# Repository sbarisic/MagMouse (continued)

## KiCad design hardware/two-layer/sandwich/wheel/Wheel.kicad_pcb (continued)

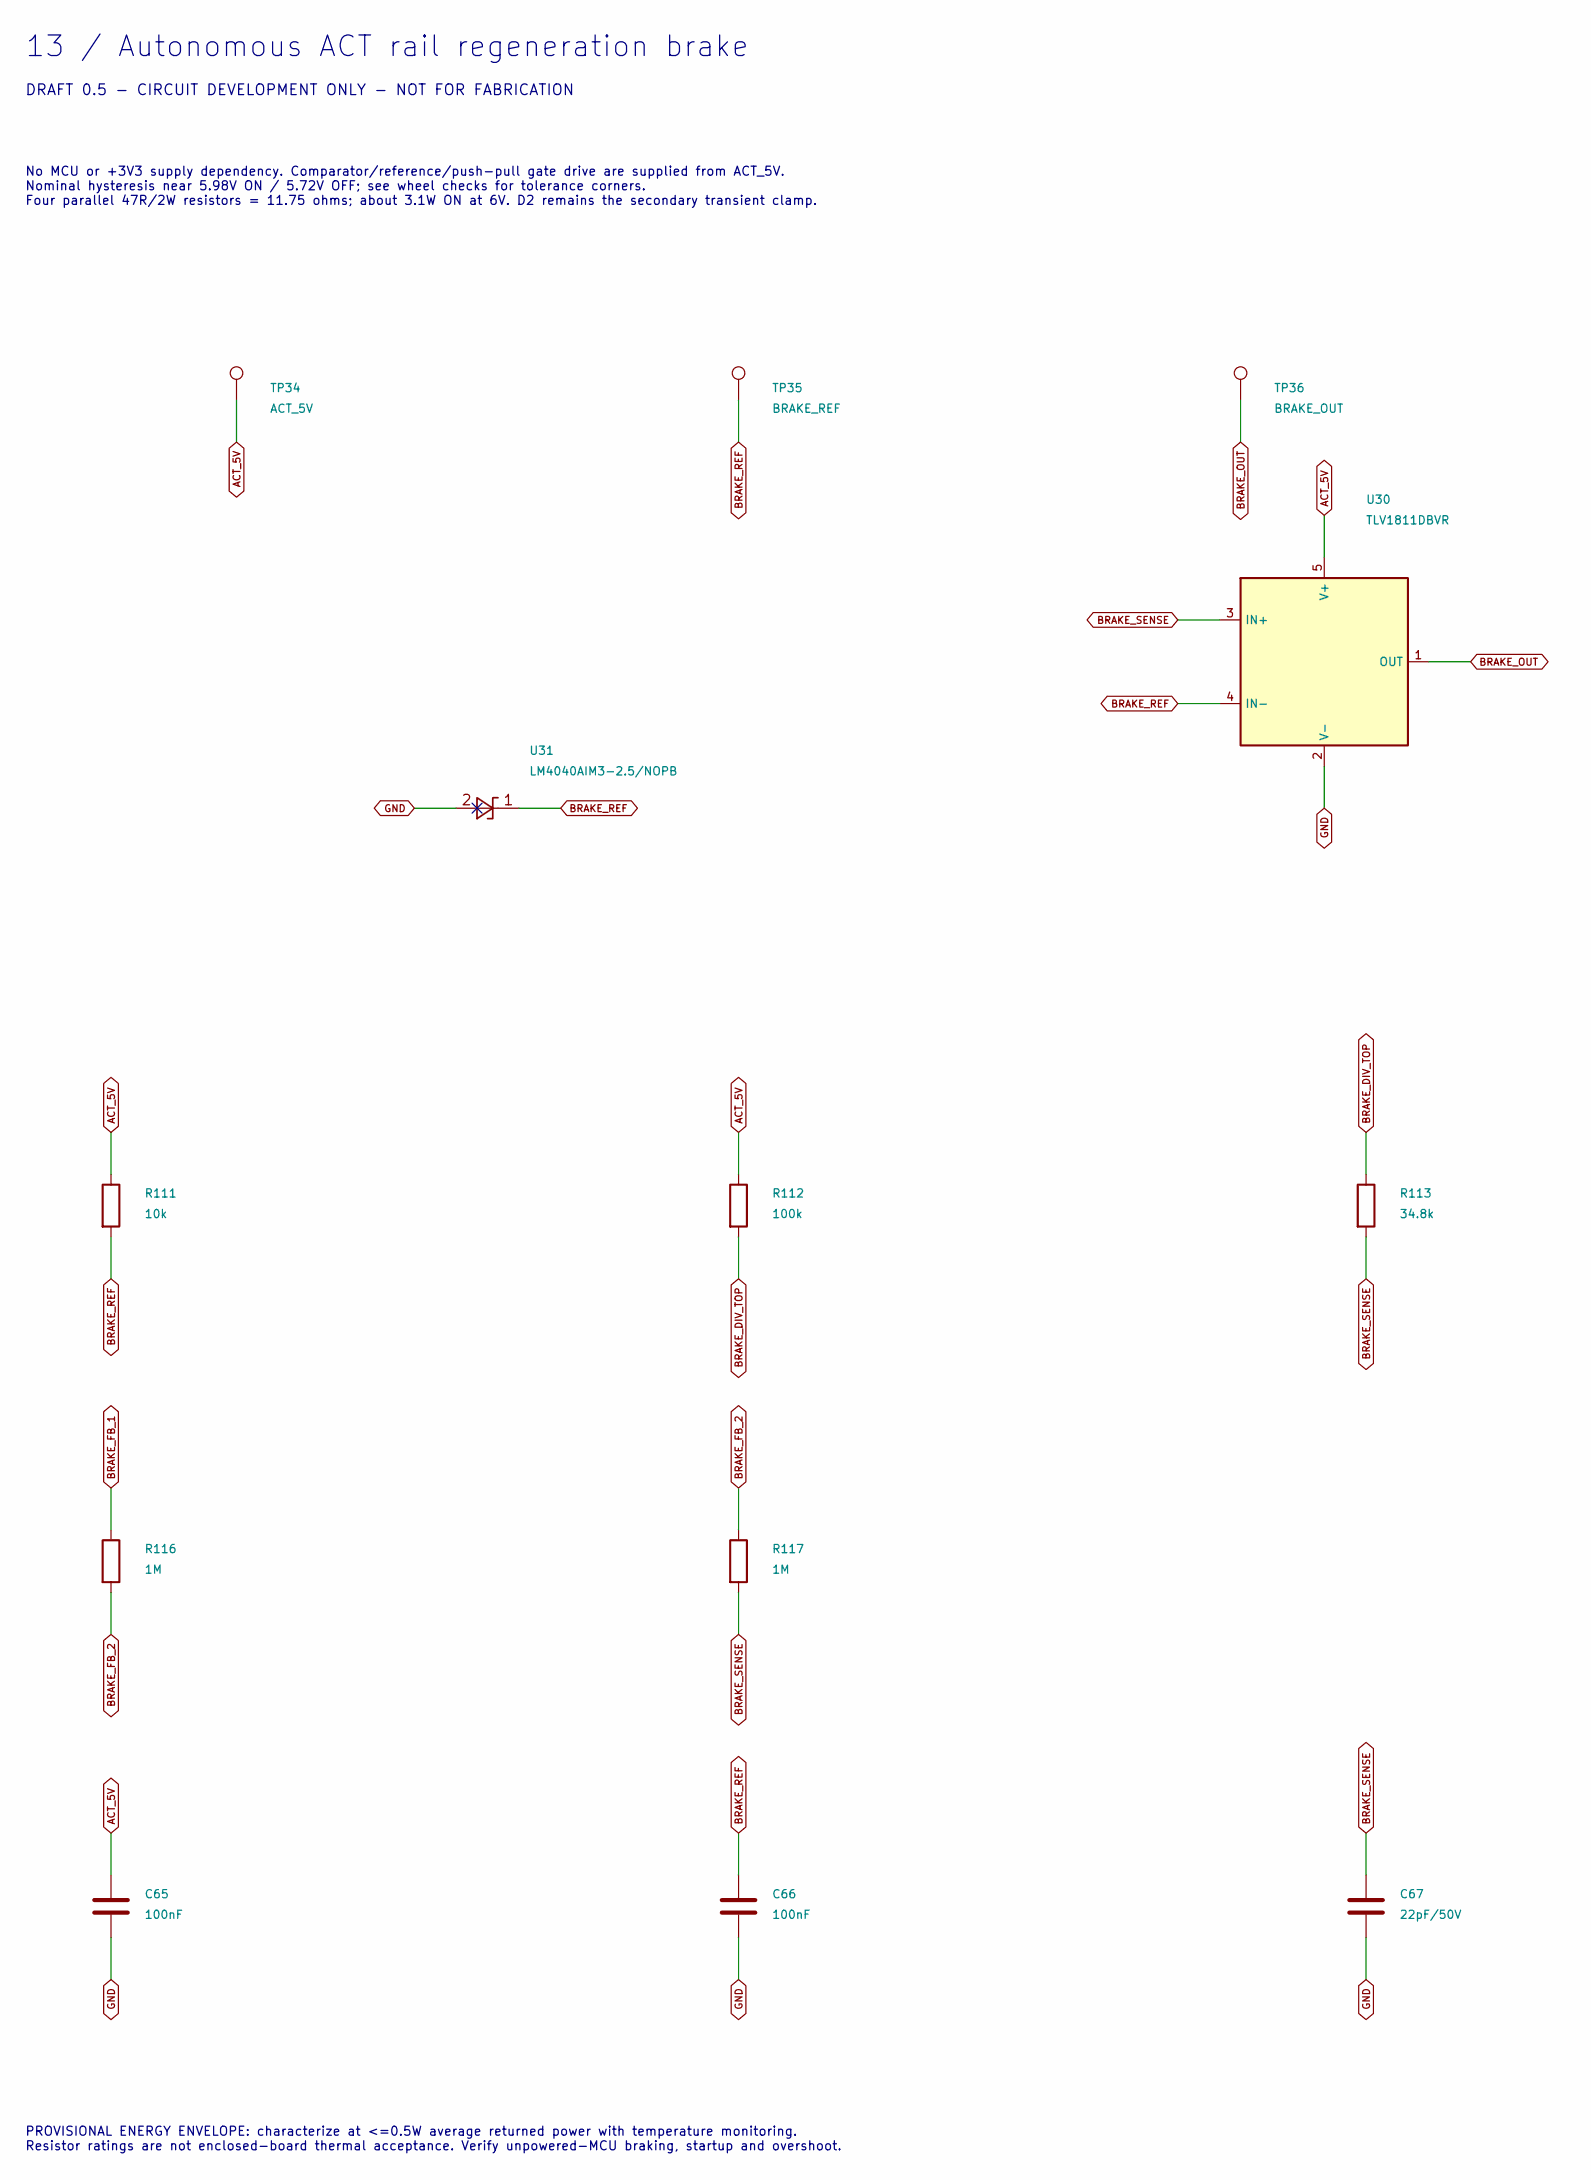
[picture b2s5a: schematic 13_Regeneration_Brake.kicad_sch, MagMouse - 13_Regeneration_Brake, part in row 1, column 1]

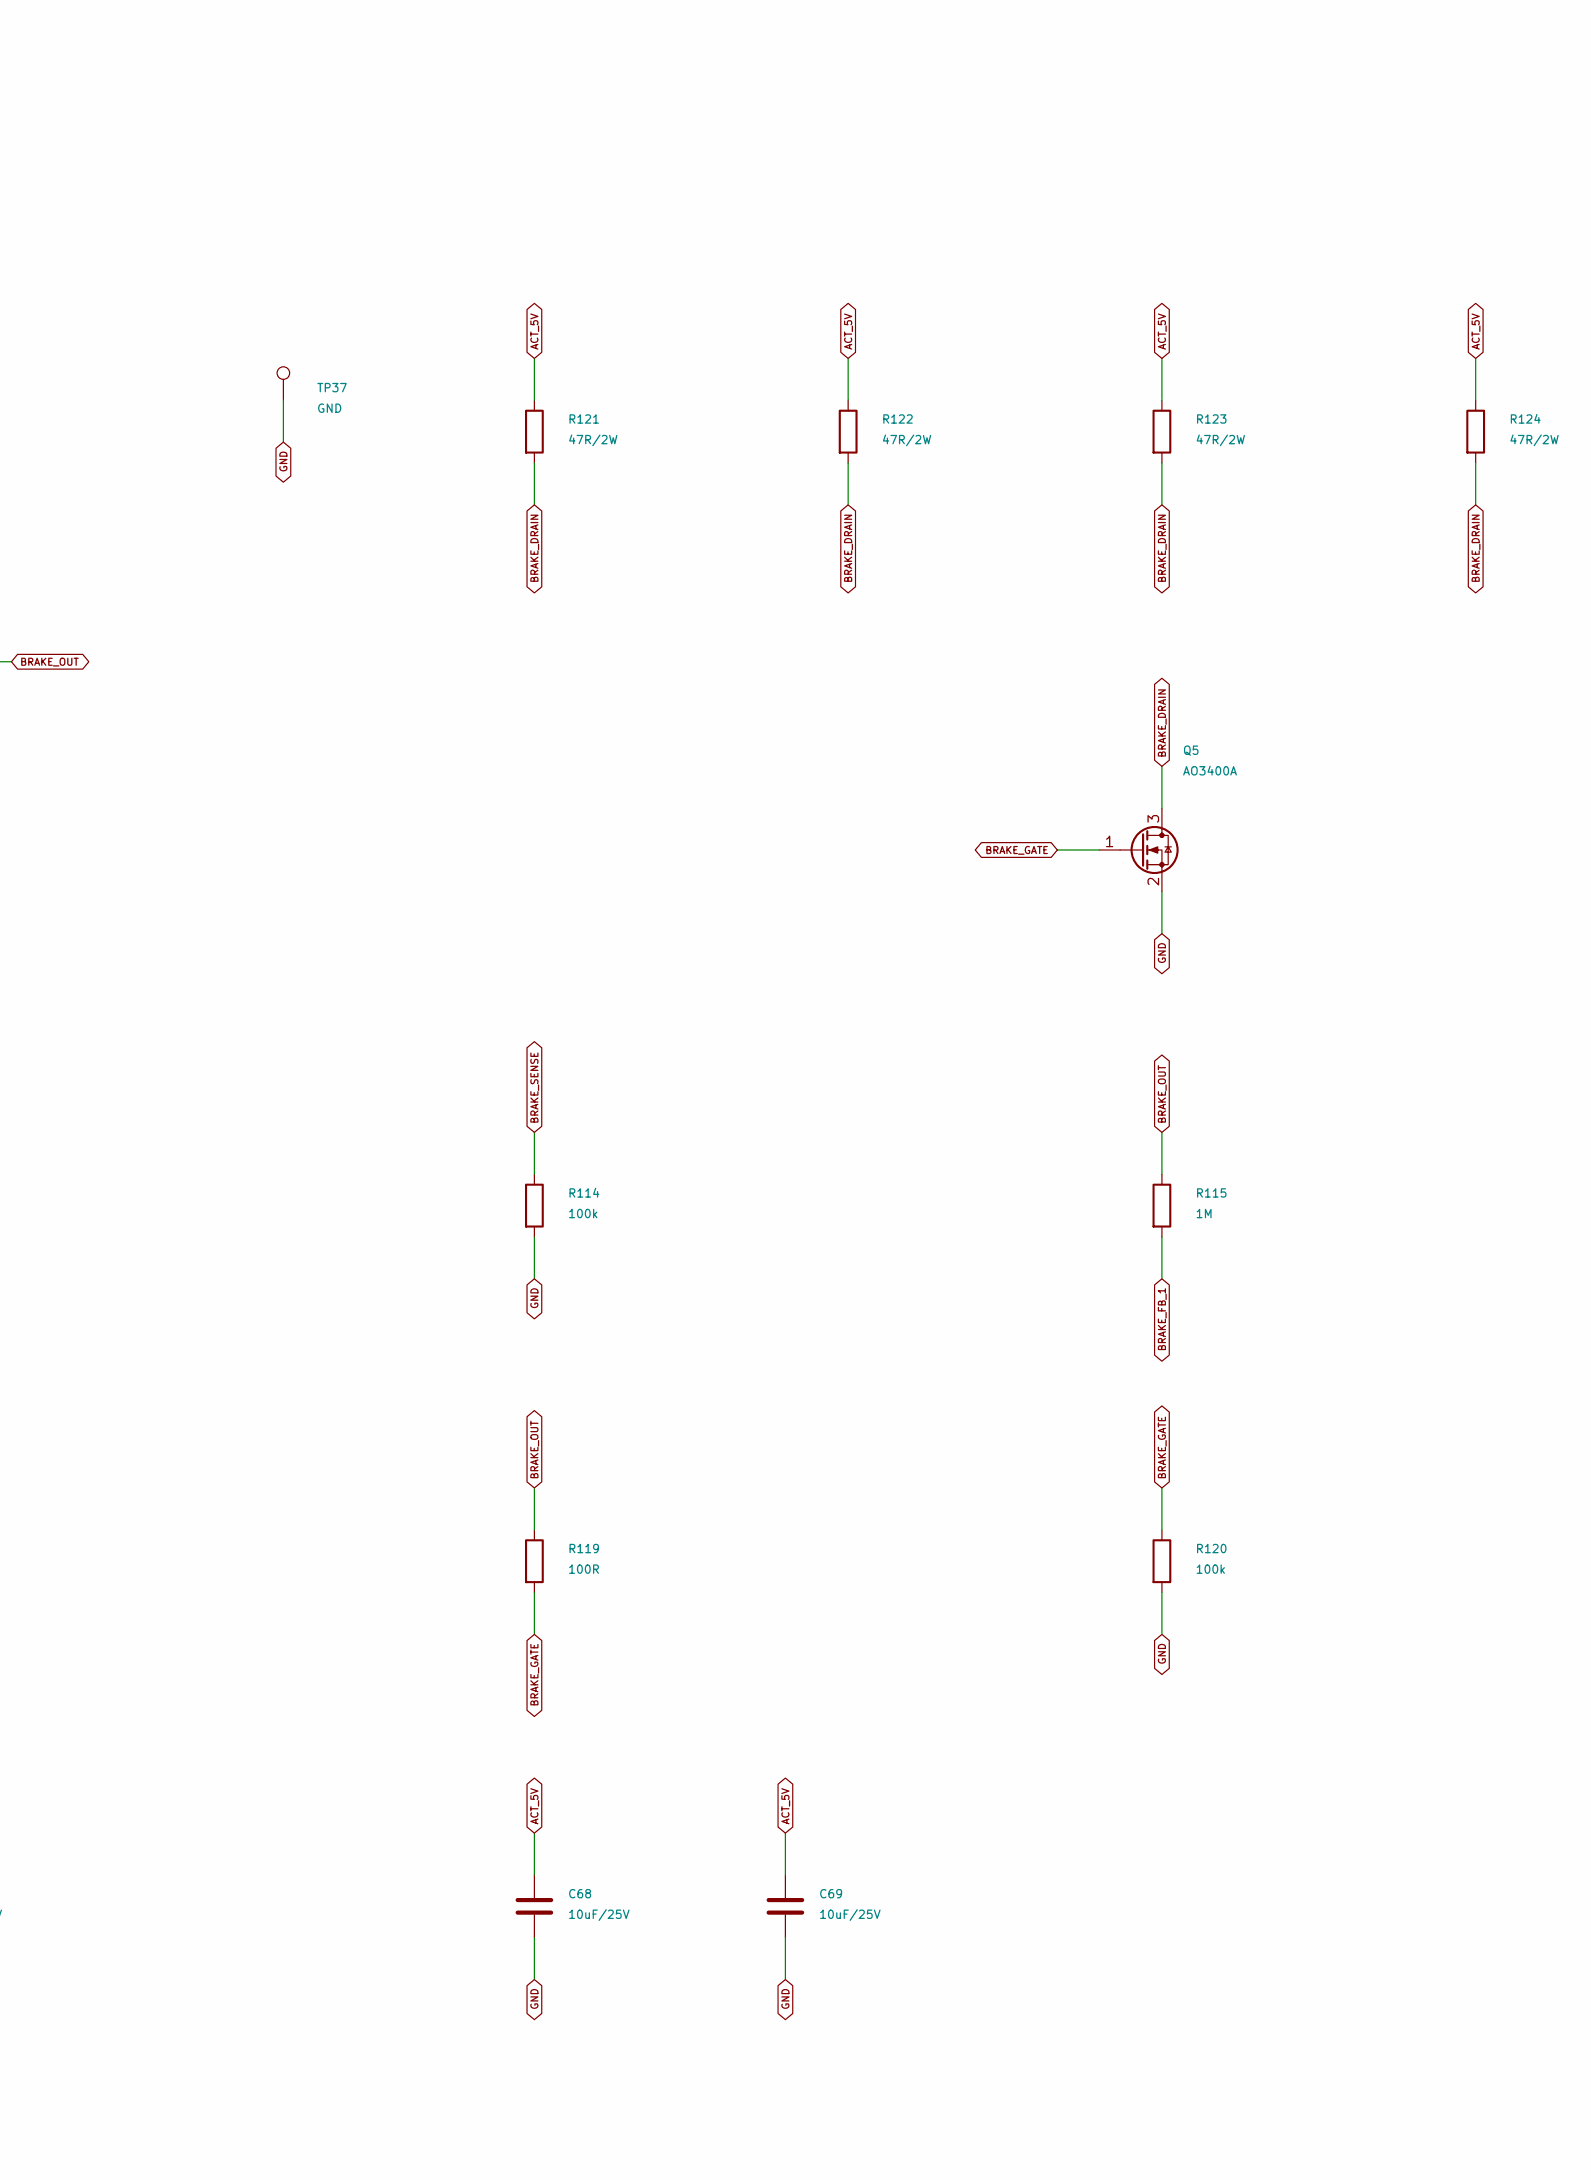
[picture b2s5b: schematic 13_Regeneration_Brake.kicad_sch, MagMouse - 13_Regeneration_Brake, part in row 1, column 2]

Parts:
C65, C66: 100nF; C_1206_3216Metric; Rating 50 V, X7R, 10%; MPN CC1206KRX7R9BB104
C67: 22pF/50V; C_1206_3216Metric; Rating 50 V, C0G/NP0, 5%; MPN CC1206JRNPO9BN220
C68, C69: 10uF/25V; C_1206_3216Metric; Rating 25 V, X5R, 10%; MPN CL31A106KAHNNNE
Q5: AO3400A; SOT-23; MPN AO3400A; LCSC C20917
R111: 10k; R_1206_3216Metric; Rating 0.25 W, 1%; MPN RC1206FR-0710KL
R112, R114, R120: 100k; R_1206_3216Metric; Rating 0.25 W, 1%; MPN RC1206FR-07100KL
R113: 34.8k; R_1206_3216Metric; Rating 0.25 W, 1%; MPN RC1206FR-0734K8L
R115, R116, R117: 1M; R_1206_3216Metric; Rating 0.25 W, 1%; MPN RC1206FR-071ML
R119: 100R; R_1206_3216Metric; Rating 0.25 W, 1%; MPN RC1206FR-07100RL
R121, R122, R123, R124: 47R/2W; R_2512_6332Metric; MPN RC2512JK-7W47RL; LCSC C136992
TP34: ACT_5V; TestPoint_Pad_D1.0mm
TP35: BRAKE_REF; TestPoint_Pad_D1.0mm
TP36: BRAKE_OUT; TestPoint_Pad_D1.0mm
TP37: GND; TestPoint_Pad_D1.0mm
U30: TLV1811DBVR; SOT-23-5; MPN TLV1811DBVR; LCSC C5373003
U31: LM4040AIM3-2.5/NOPB; SOT-23; MPN LM4040AIM3-2.5/NOPB; LCSC C139302

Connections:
ACT_5V: C65.1, C68.1, C69.1, R111.1, R112.1, R121.1, R122.1, R123.1, R124.1, TP34.1, U30.5 (V+); also elsewhere on the board
BRAKE_DIV_TOP: R112.2, R113.1
BRAKE_DRAIN: Q5.3 (D), R121.2, R122.2, R123.2, R124.2
BRAKE_FB_1: R115.2, R116.1
BRAKE_FB_2: R116.2, R117.1
BRAKE_GATE: Q5.1 (G), R119.2, R120.1
BRAKE_OUT: R115.1, R119.1, TP36.1, U30.1 (OUT)
BRAKE_REF: C66.1, R111.2, TP35.1, U30.4 (IN-), U31.1 (K)
BRAKE_SENSE: C67.1, R113.2, R114.1, R117.2, U30.3 (IN+)
GND: C65.2, C66.2, C67.2, C68.2, C69.2, Q5.2 (S), R114.2, R120.2, TP37.1, U30.2 (V-), U31.2 (A); also elsewhere on the board

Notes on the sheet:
13 / Autonomous ACT rail regeneration brake
DRAFT 0.5 - CIRCUIT DEVELOPMENT ONLY - NOT FOR FABRICATION
No MCU or +3V3 supply dependency. Comparator/reference/push-pull gate drive are supplied from ACT_5V. Nominal hysteresis near 5.98V ON / 5.72V OFF; see wheel checks for tolerance corners. Four parallel 47R/2W resistors = 11.75 ohms; about 3.1W ON at 6V. D2 remains the secondary transient clamp.
PROVISIONAL ENERGY ENVELOPE: characterize at <=0.5W average returned power with temperature monitoring. Resistor ratings are not enclosed-board thermal acceptance. Verify unpowered-MCU braking, startup and overshoot.

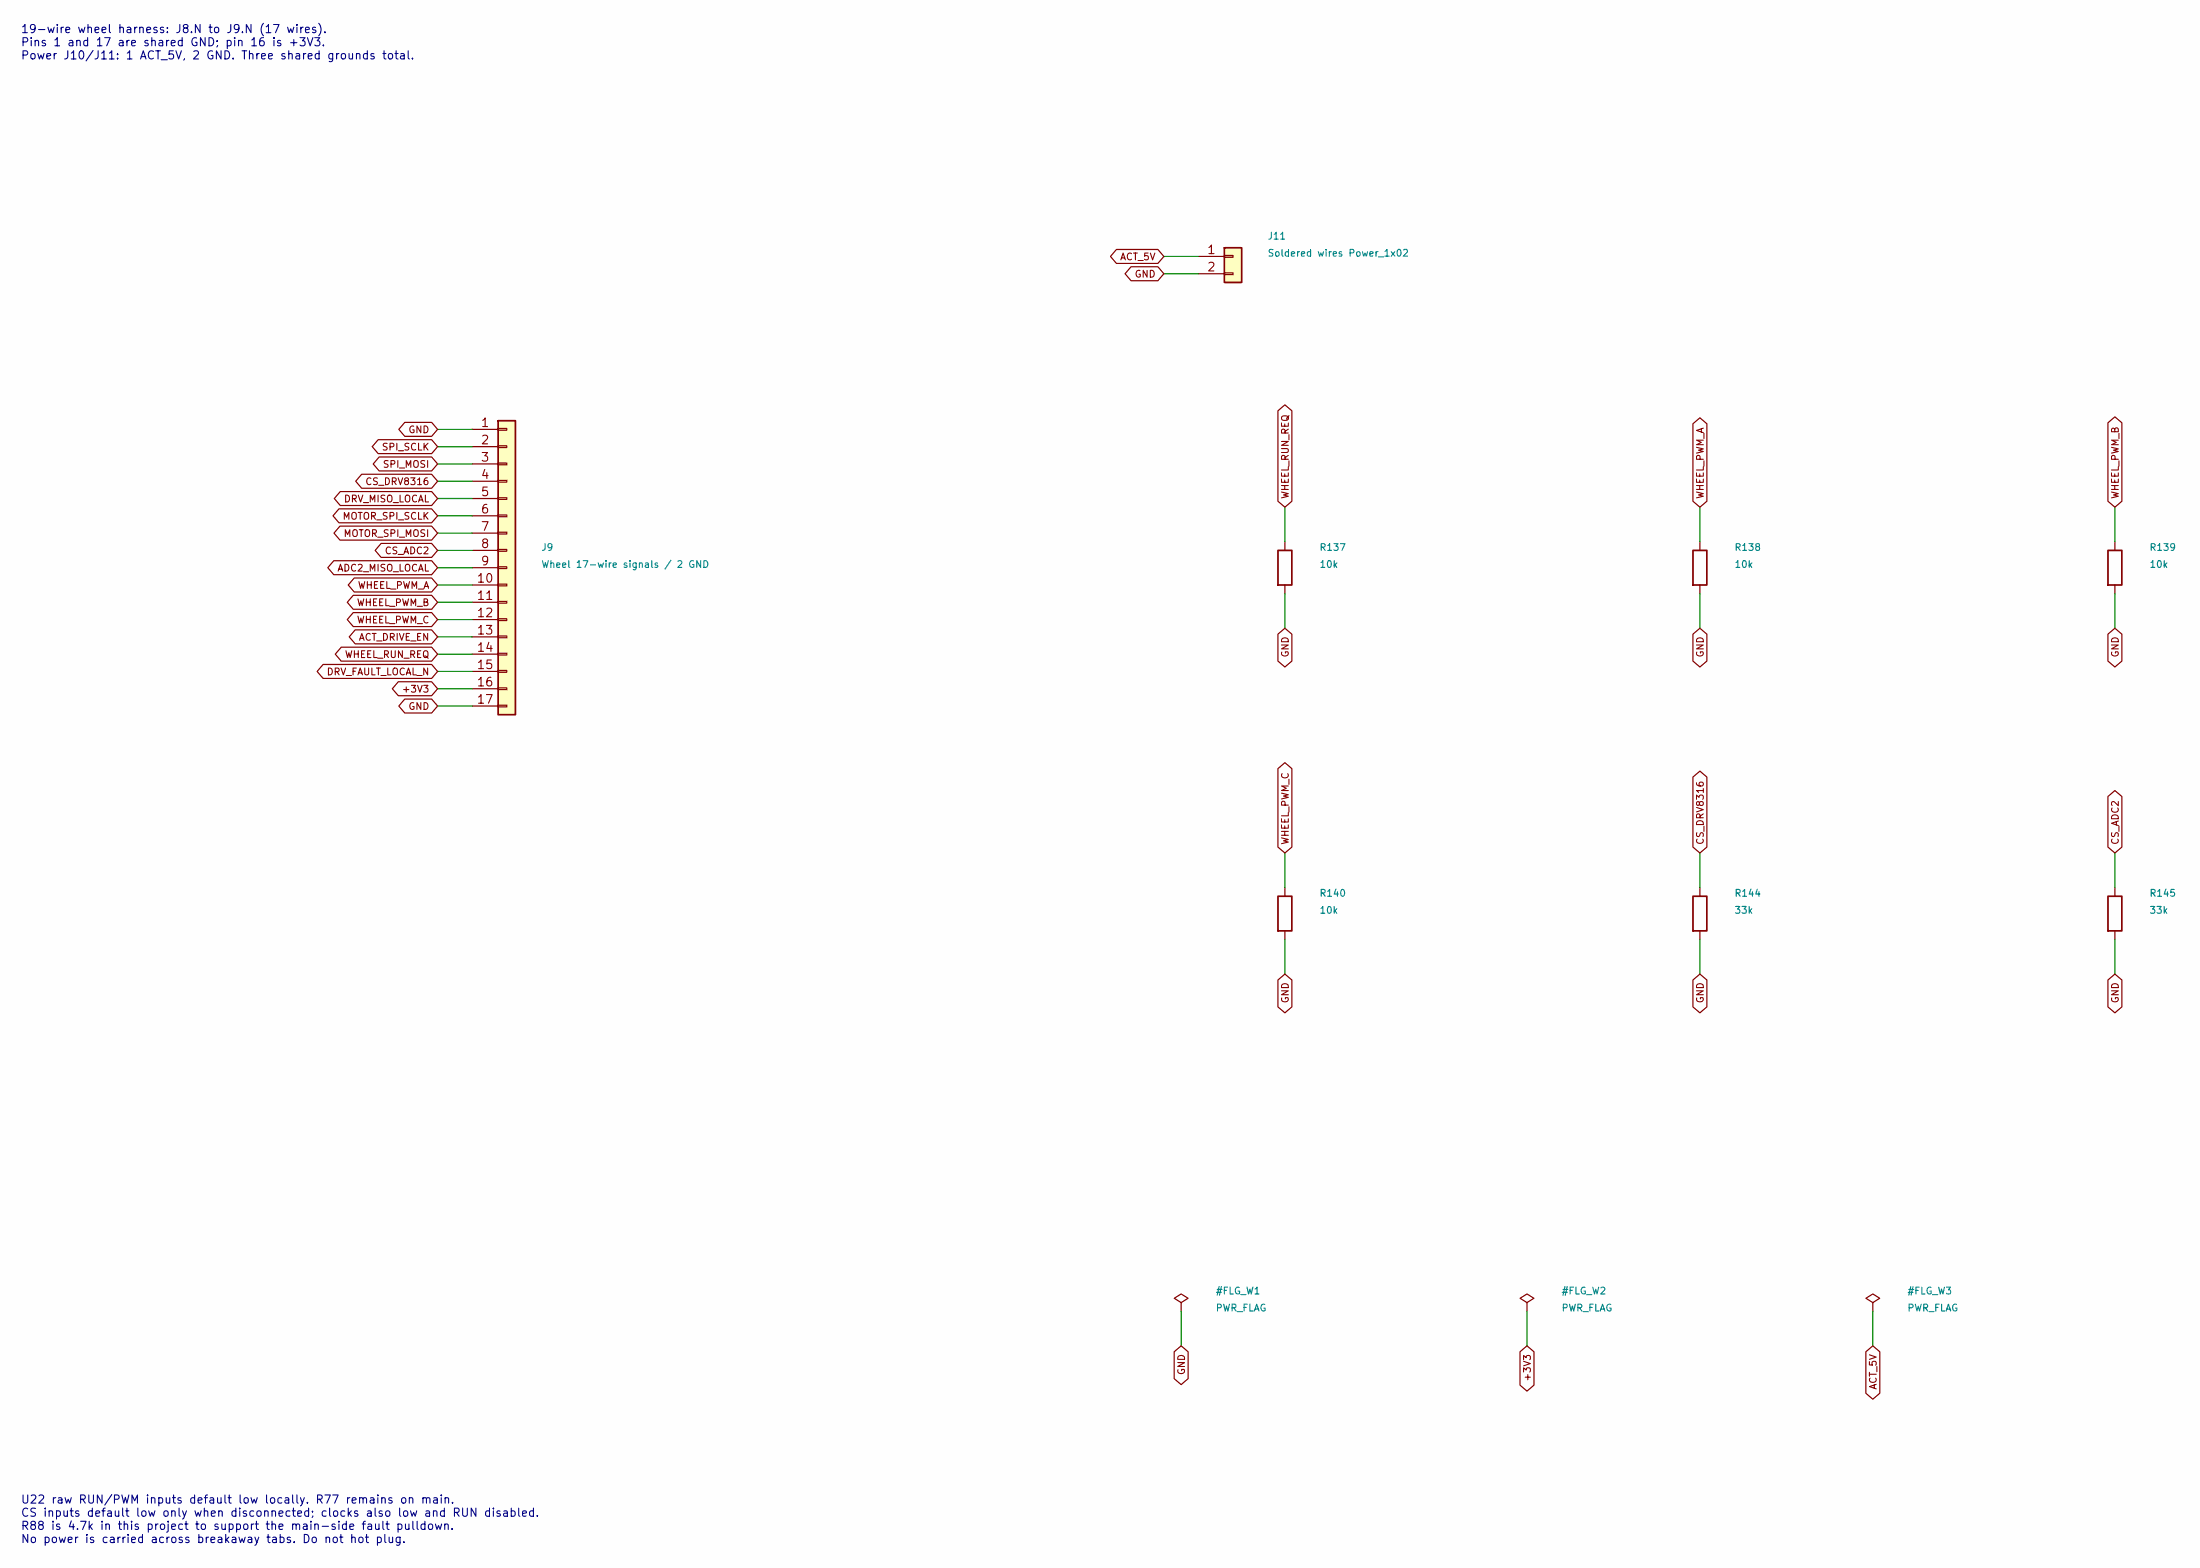
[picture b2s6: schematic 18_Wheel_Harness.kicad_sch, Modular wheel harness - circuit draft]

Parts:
J9: Wheel 17-wire signals / 2 GND; Wire_Wheel_17_P2.54mm
J11: Soldered wires Power_1x02; Wire_Power_1x02_P2.54mm
R137, R138, R139, R140: 10k; R_1206_3216Metric; Rating 0.25 W, 1%; MPN RC1206FR-0710KL
R144, R145: 33k; R_1206_3216Metric; Rating 0.25 W, 1%; MPN RC1206FR-0733KL

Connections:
+3V3: J9.16; also elsewhere on the board
ACT_5V: J11.1; also elsewhere on the board
ACT_DRIVE_EN: J9.13; also elsewhere on the board
ADC2_MISO_LOCAL: J9.9; also elsewhere on the board
CS_ADC2: J9.8, R145.1; also elsewhere on the board
CS_DRV8316: J9.4, R144.1; also elsewhere on the board
DRV_FAULT_LOCAL_N: J9.15; also elsewhere on the board
DRV_MISO_LOCAL: J9.5; also elsewhere on the board
GND: J9.1, J9.17, J11.2, R137.2, R138.2, R139.2, R140.2, R144.2, R145.2; also elsewhere on the board
MOTOR_SPI_MOSI: J9.7; also elsewhere on the board
MOTOR_SPI_SCLK: J9.6; also elsewhere on the board
SPI_MOSI: J9.3; also elsewhere on the board
SPI_SCLK: J9.2; also elsewhere on the board
WHEEL_PWM_A: J9.10, R138.1; also elsewhere on the board
WHEEL_PWM_B: J9.11, R139.1; also elsewhere on the board
WHEEL_PWM_C: J9.12, R140.1; also elsewhere on the board
WHEEL_RUN_REQ: J9.14, R137.1; also elsewhere on the board

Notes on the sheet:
19-wire wheel harness: J8.N to J9.N (17 wires). Pins 1 and 17 are shared GND; pin 16 is +3V3. Power J10/J11: 1 ACT_5V, 2 GND. Three shared grounds total.
U22 raw RUN/PWM inputs default low locally. R77 remains on main. CS inputs default low only when disconnected; clocks also low and RUN disabled. R88 is 4.7k in this project to support the main-side fault pulldown. No power is carried across breakaway tabs. Do not hot plug.

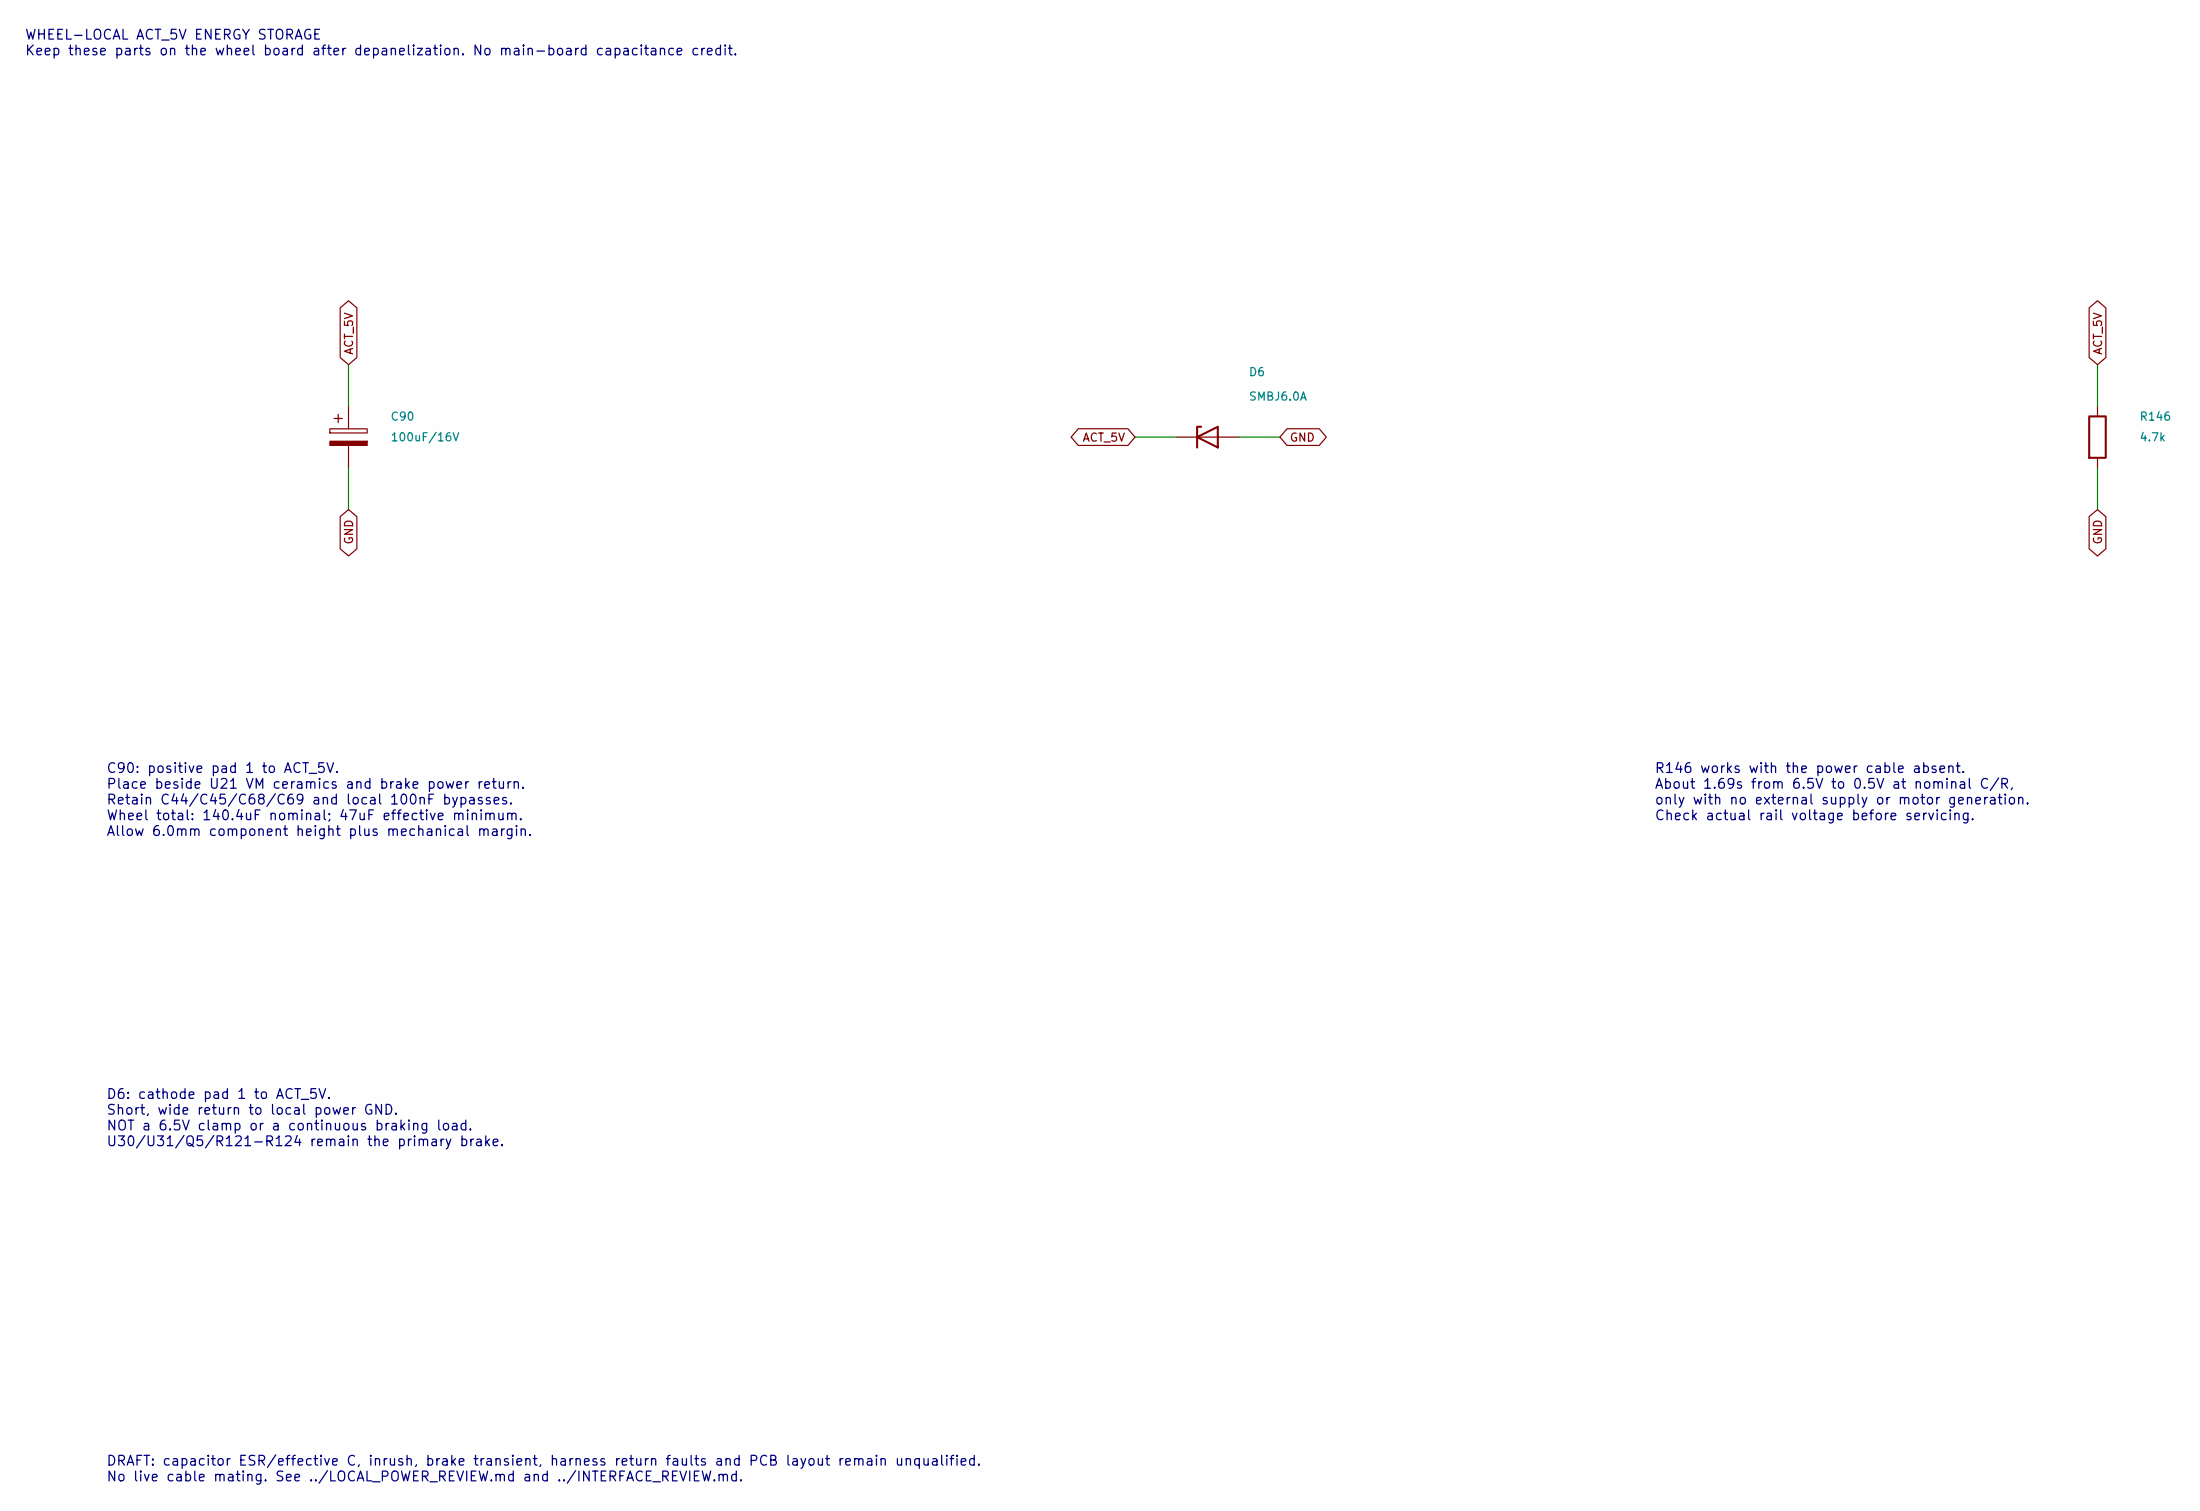
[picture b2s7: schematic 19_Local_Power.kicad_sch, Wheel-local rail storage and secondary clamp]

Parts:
C90: 100uF/16V; CP_Elec_6.3x5.9; MPN 16SVPC100M; LCSC C136275
D6: SMBJ6.0A; D_SMB; MPN SMBJ6.0A; LCSC C83270
R146: 4.7k; R_1206_3216Metric; Rating 0.25 W, 1%; MPN RC1206FR-074K7L

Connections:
ACT_5V: C90.1, D6.1 (K), R146.1; also elsewhere on the board
GND: C90.2, D6.2 (A), R146.2; also elsewhere on the board

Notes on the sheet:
WHEEL-LOCAL ACT_5V ENERGY STORAGE Keep these parts on the wheel board after depanelization. No main-board capacitance credit.
C90: positive pad 1 to ACT_5V. Place beside U21 VM ceramics and brake power return. Retain C44/C45/C68/C69 and local 100nF bypasses. Wheel total: 140.4uF nominal; 47uF effective minimum. Allow 6.0mm component height plus mechanical margin.
D6: cathode pad 1 to ACT_5V. Short, wide return to local power GND. NOT a 6.5V clamp or a continuous braking load. U30/U31/Q5/R121-R124 remain the primary brake.
R146 works with the power cable absent. About 1.69s from 6.5V to 0.5V at nominal C/R, only with no external supply or motor generation. Check actual rail voltage before servicing.
DRAFT: capacitor ESR/effective C, inrush, brake transient, harness return faults and PCB layout remain unqualified. No live cable mating. See ../LOCAL_POWER_REVIEW.md and ../INTERFACE_REVIEW.md.

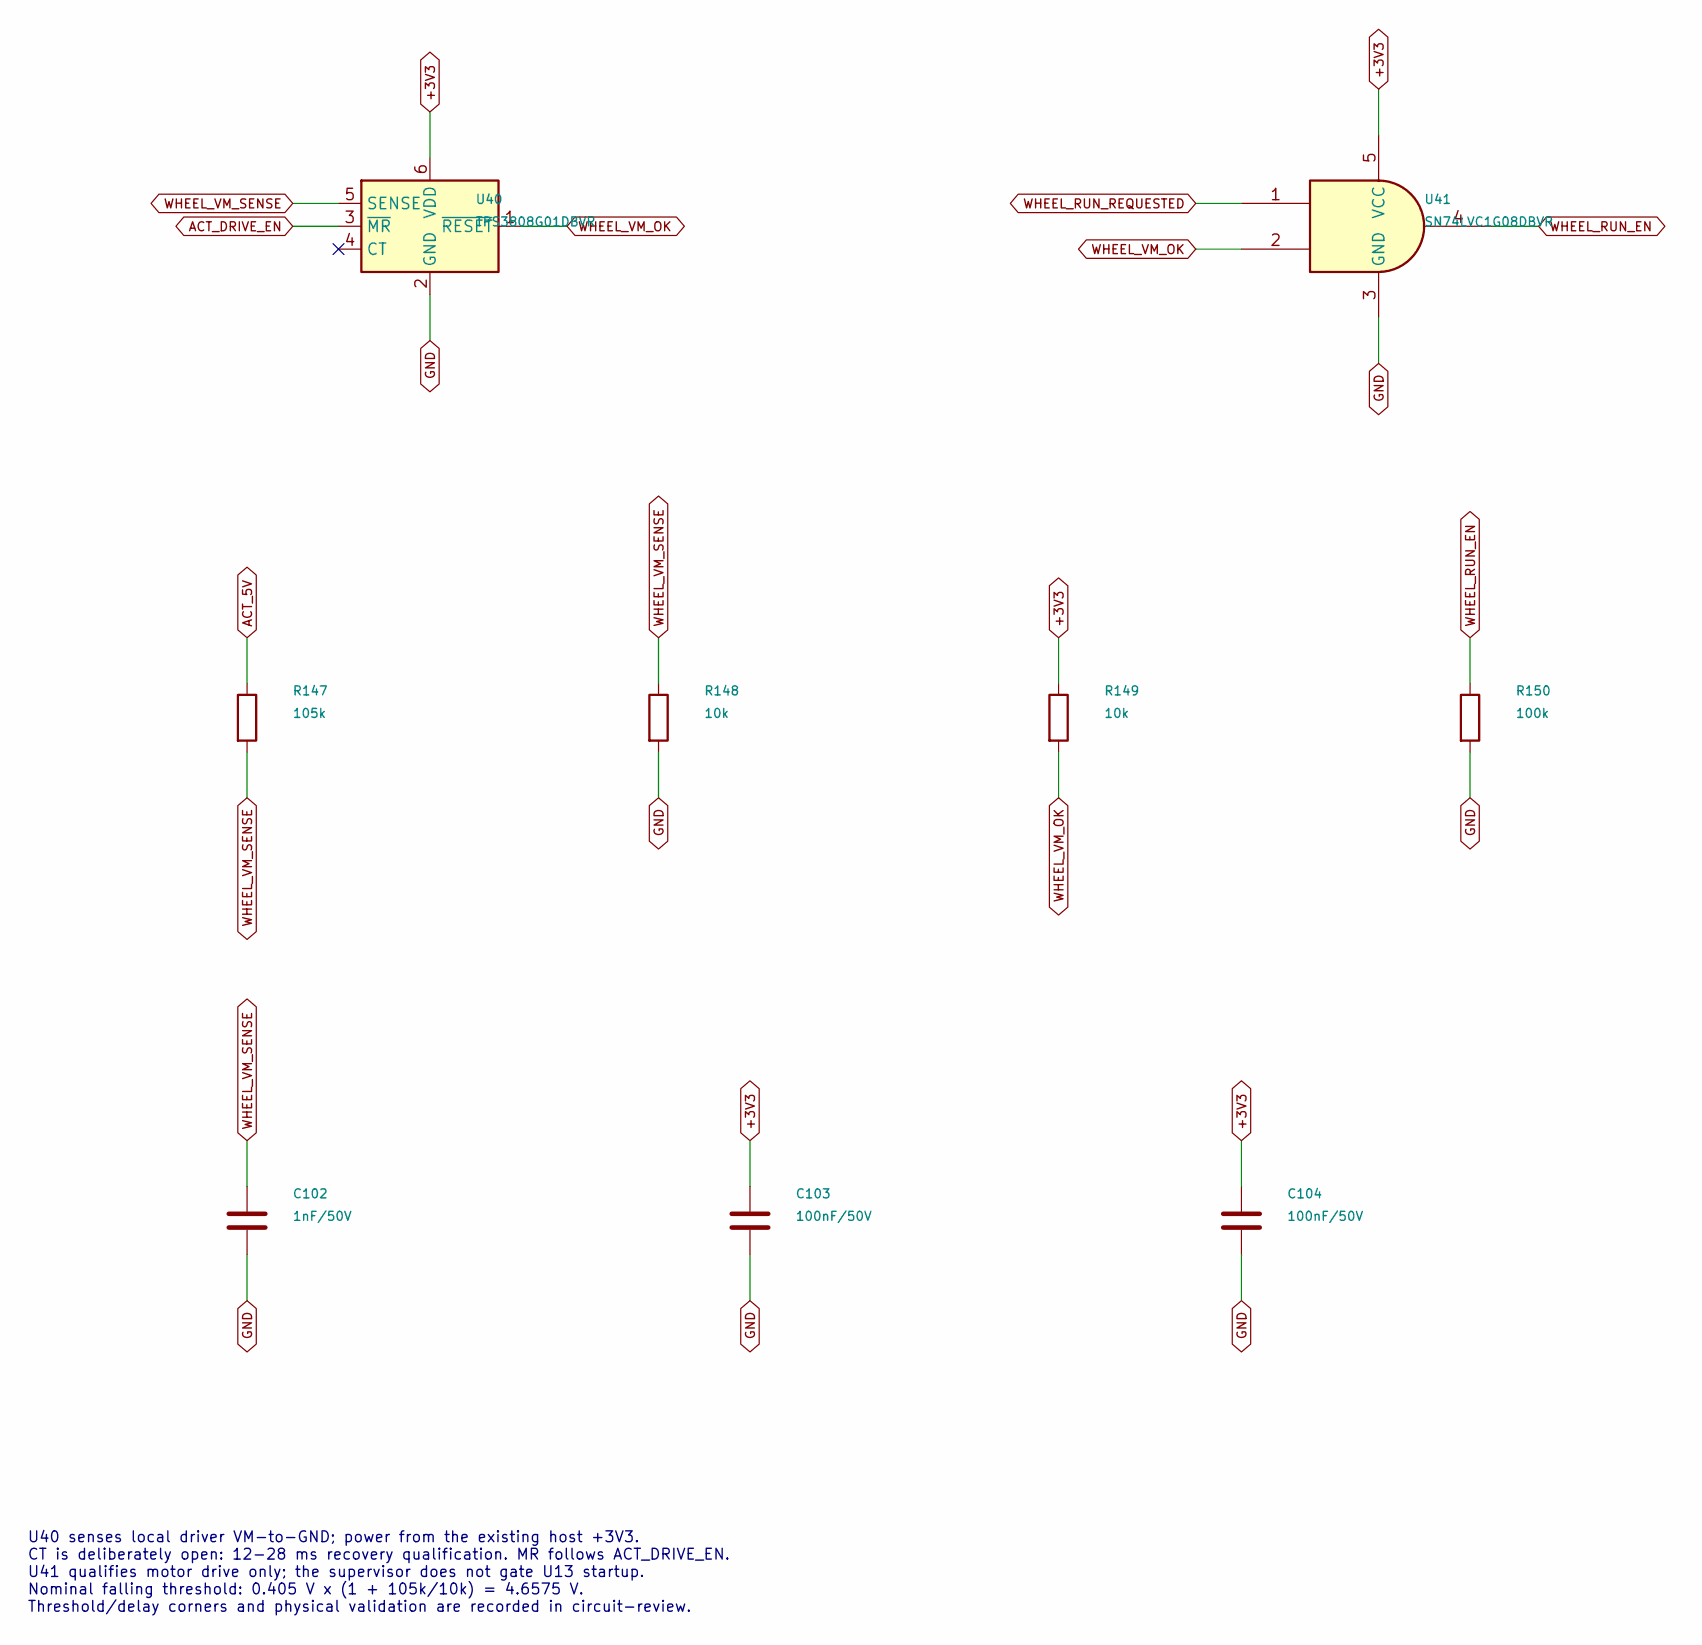
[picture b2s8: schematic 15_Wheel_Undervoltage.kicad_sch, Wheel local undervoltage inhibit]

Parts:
C102: 1nF/50V; C_1206_3216Metric; Rating C0G, 5%, 50 V; MPN CL31C102JBCNNNC
C103, C104: 100nF/50V; C_1206_3216Metric; Rating X7R, 10%, 50 V; MPN CL31B104KBCNNNC
R147: 105k; R_1206_3216Metric; Rating 0.1%, 25 ppm/K; MPN TNPW1206105KBEEA
R148: 10k; R_1206_3216Metric; Rating 0.1%, 25 ppm/K; MPN TNPW120610K0BEEA
R149: 10k; R_1206_3216Metric; Rating 1%, 0.25 W; MPN RC1206FR-0710KL
R150: 100k; R_1206_3216Metric; Rating 1%, 0.25 W; MPN RC1206FR-07100KL
U40: TPS3808G01DBVR; SOT-23-6; MPN TPS3808G01DBVR
U41: SN74LVC1G08DBVR; SOT-23-5; MPN SN74LVC1G08DBVR

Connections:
+3V3: C103.1, C104.1, R149.1, U40.6 (VDD), U41.5 (VCC); also elsewhere on the board
ACT_5V: R147.1; also elsewhere on the board
ACT_DRIVE_EN: U40.3 (~MR); also elsewhere on the board
GND: C102.2, C103.2, C104.2, R148.2, R150.2, U40.2 (GND), U41.3 (GND); also elsewhere on the board
WHEEL_RUN_EN: R150.1, U41.4; also elsewhere on the board
WHEEL_RUN_REQUESTED: U41.1; also elsewhere on the board
WHEEL_VM_OK: R149.2, U40.1 (~RESET), U41.2
WHEEL_VM_SENSE: C102.1, R147.2, R148.1, U40.5 (SENSE)

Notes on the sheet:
U40 senses local driver VM-to-GND; power from the existing host +3V3. CT is deliberately open: 12-28 ms recovery qualification. MR follows ACT_DRIVE_EN. U41 qualifies motor drive only; the supervisor does not gate U13 startup. Nominal falling threshold: 0.405 V x (1 + 105k/10k) = 4.6575 V. Threshol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

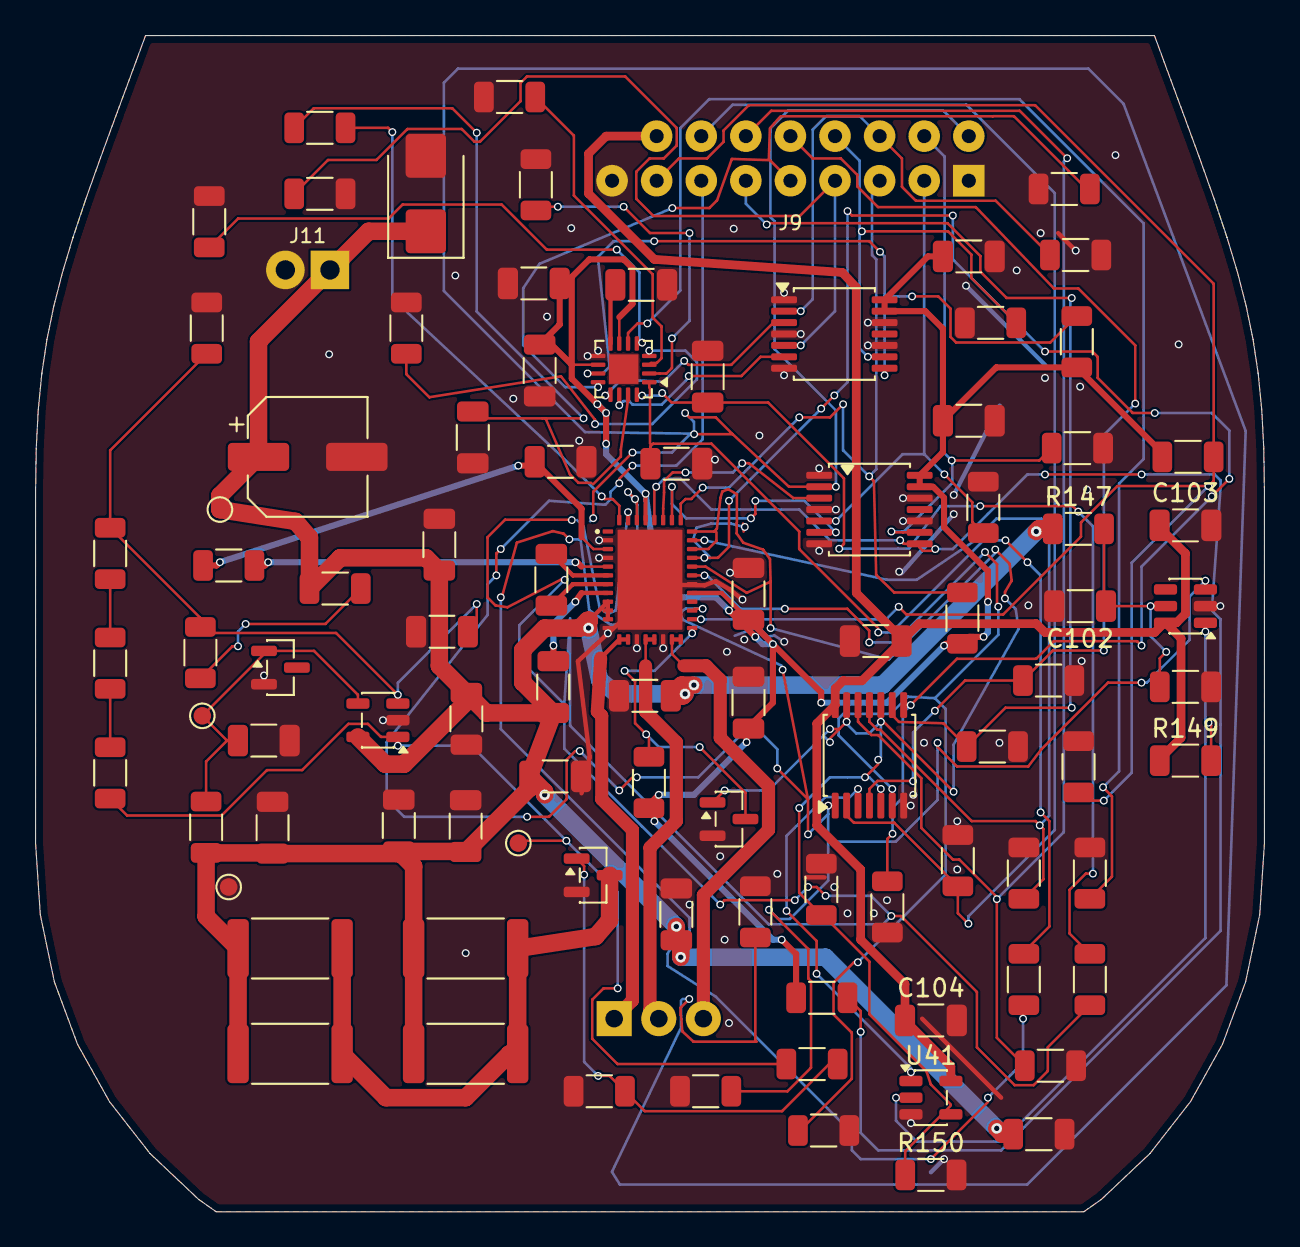
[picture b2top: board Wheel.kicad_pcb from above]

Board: 2 copper layers, 70.0 x 67.0 mm, 96 parts (0 on the bottom side), 60 nets.

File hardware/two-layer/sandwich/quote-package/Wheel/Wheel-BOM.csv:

Comment,Designator,Footprint,LCSC Part #,Manufacturer,MPN,Quantity
1nF/50V,C102,C_1206_3216Metric,,Samsung Electro-Mechanics,CL31C102JBCNNNC,1
100nF/50V,"C103,C104",C_1206_3216Metric,,Samsung Electro-Mechanics,CL31B104KBCNNNC,2
100nF,"C41,C42,C43,C49,C51,C52,C54,C65,C66",C_1206_3216Metric,,YAGEO,CC1206KRX7R9BB104,9
10uF/25V,"C44,C45,C68,C69",C_1206_3216Metric,,Samsung Electro-Mechanics,CL31A106KAHNNNE,4
1uF/50V,"C46,C48,C56,C57,C58",C_1206_3216Metric,,Samsung Electro-Mechanics,CL31B105KBHNNNE,5
47nF/50V,C47,C_1206_3216Metric,,YAGEO,CC1206KRX7R9BB473,1
22uF/25V,C50,C_1206_3216Metric,,Samsung Electro-Mechanics,CL31A226KAHNNNE,1
22pF/50V,"C59,C60,C61,C67",C_1206_3216Metric,,YAGEO,CC1206JRNPO9BN220,4
100uF/16V,C90,CP_Elec_6.3x5.9,C136275,Panasonic,16SVPC100M,1
SMBJ6.0A,D6,D_SMB,C83270,Littelfuse,SMBJ6.0A,1
2N7002,Q4,SOT-23,C8545,Jiangsu Changjing Electronics Technology,2N7002,1
AO3400A,Q5,SOT-23,C20917,Alpha & Omega Semiconductor,AO3400A,1
100k,"R100,R112,R114,R120,R150,R83,R89,R90,R91,R92,R94,R95,R96,R97",R_1206_3216Metric,,YAGEO,RC1206FR-07100KL,14
330R,"R102,R103,R104",R_1206_3216Metric,,YAGEO,RC1206FR-07330RL,3
0R,"R105,R106,R107,R108,R109",R_1206_3216Metric,,YAGEO,RC1206JR-070RL,5
10k,"R111,R137,R138,R139,R140,R149,R82,R84,R86,R98",R_1206_3216Metric,,YAGEO,RC1206FR-0710KL,10
34.8k,R113,R_1206_3216Metric,,YAGEO,RC1206FR-0734K8L,1
1M,"R115,R116,R117",R_1206_3216Metric,,YAGEO,RC1206FR-071ML,3
100R,R119,R_1206_3216Metric,,YAGEO,RC1206FR-07100RL,1
47R/2W,"R121,R122,R123,R124",R_2512_6332Metric,C136992,YAGEO,RC2512JK-7W47RL,4
33k,"R144,R145",R_1206_3216Metric,,YAGEO,RC1206FR-0733KL,2
4.7k,"R146,R87,R88",R_1206_3216Metric,,YAGEO,RC1206FR-074K7L,3
105k,R147,R_1206_3216Metric,,Vishay,TNPW1206105KBEEA,1
10k,R148,R_1206_3216Metric,,Vishay,TNPW120610K0BEEA,1
22R,R81,R_1206_3216Metric,,YAGEO,RC1206FR-0722RL,1
DRV8316RRGFR,U21,Texas_RGF0040E,C5218861,Texas Instruments,DRV8316RRGFR,1
SN74LVC08APWR,U22,TSSOP-14_4.4x5mm_P0.65mm,C465737,Texas Instruments,SN74LVC08APWR,1
ADS7038IRTER,U23,WQFN-16-1EP_3x3mm_P0.5mm_EP1.68x1.68mm,C2871580,Texas Instruments,ADS7038IRTER,1
"74LVC125APW,118",U24,TSSOP-14_4.4x5mm_P0.65mm_InsetPin1,C6059,Nexperia,"74LVC125APW,118",1
"74LVC125APW,118",U26,TSSOP-14_4.4x5mm_P0.65mm,C6059,Nexperia,"74LVC125APW,118",1
TLV1811DBVR,U30,SOT-23-5,C5373003,Texas Instruments,TLV1811DBVR,1
LM4040AIM3-2.5/NOPB,U31,SOT-23,C139302,Texas Instruments,LM4040AIM3-2.5/NOPB,1
TPS3808G01DBVR,U40,SOT-23-6,,Texas Instruments,TPS3808G01DBVR,1
SN74LVC1G08DBVR,U41,SOT-23-5,,Texas Instruments,SN74LVC1G08DBVR,1
